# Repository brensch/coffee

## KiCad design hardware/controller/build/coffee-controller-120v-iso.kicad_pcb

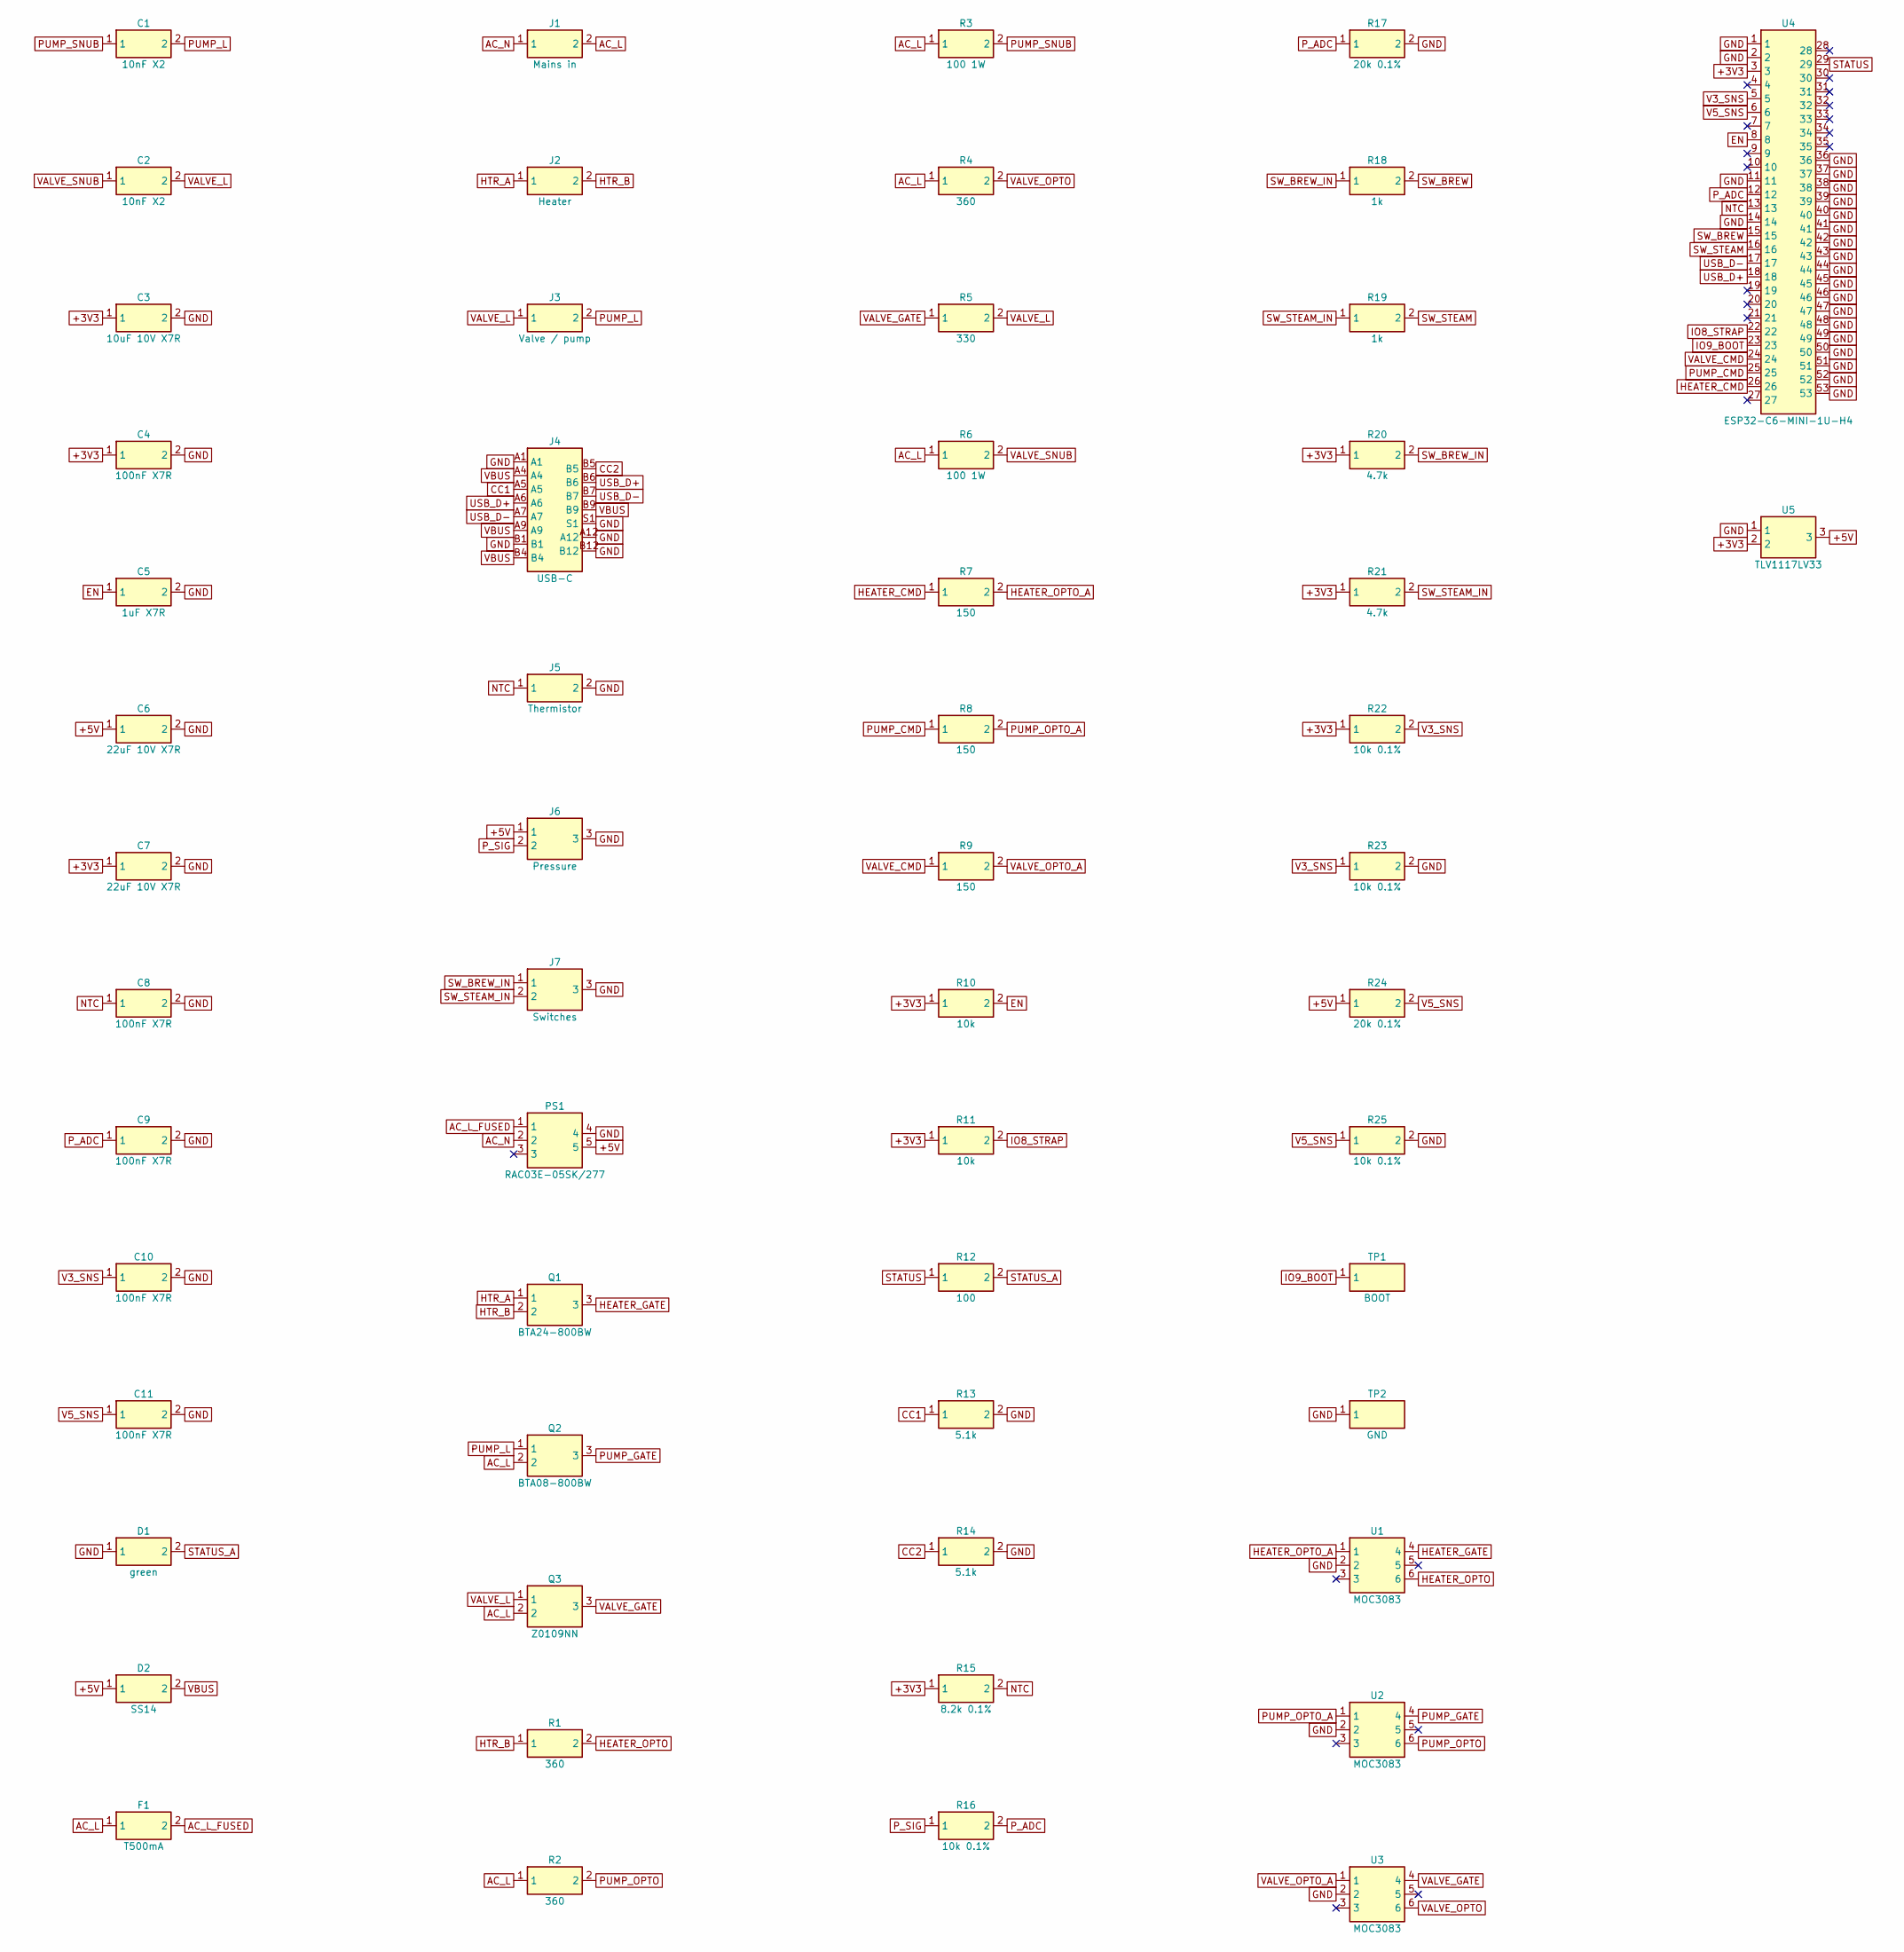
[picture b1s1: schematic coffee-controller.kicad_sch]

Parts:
C1, C2: 10nF X2; C_2220_Murata_GA355; MPN Murata GA355QR7GB103KW01L (10 nF X2 250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
C3: 10uF 10V X7R; C_0805_2012Metric
C4, C8, C9, C10, C11: 100nF X7R; C_0603_1608Metric
C5: 1uF X7R; C_0603_1608Metric
C6, C7: 22uF 10V X7R; C_0805_2012Metric; MPN Murata GRM21BZ71A226ME15L
D1: green; LED_0603_1608Metric
D2: SS14; D_SMA; MPN SS14
F1: T500mA; Fuse_Littelfuse_372_D8.50mm; MPN Littelfuse 37205000411 (TR5, 500 mA slo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
J1: Mains in; TerminalBlock_Phoenix_MKDS-1,5-2-5.08_1x02_P5.08mm_Horizont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; MPN Phoenix Contact MKDS 1,5/2-5.08 (171572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
J2: Heater; TerminalBlock_Phoenix_MKDS-3-2-5.08_1x02_P5.08mm_Horizontal; MPN Phoenix Contact MKDS 3/2-5.08 (1711725)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
J3: Valve / pump; TerminalBlock_Phoenix_MKDS-1,5-2-5.08_1x02_P5.08mm_Horizont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; MPN Phoenix Contact MKDS 1,5/2-5.08 (171572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
J4: USB-C; USB_C_Receptacle_GCT_USB4105-xx-A_16P_TopMnt_Horizontal; MPN GCT USB4105-GF-A
J5: Thermistor; JST_PH_B2B-PH-K_1x02_P2.00mm_Vertical
J6: Pressure; JST_PH_B3B-PH-K_1x03_P2.00mm_Vertical
J7: Switches; JST_PH_B3B-PH-K_1x03_P2.00mm_Vertical
PS1: RAC03E-05SK/277; RAC03E-K_277; MPN RECOM RAC03E-05SK/277
Q1: BTA24-800BW; TO-220-3_Vertical_Drill1.2; MPN ST BTA24-800BWRG (25 A, 800 V, insulate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
Q2: BTA08-800BW; TO-220-3_Vertical_Drill1.2; MPN ST BTA08-800BWRG (8 A, 800 V, insulated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
Q3: Z0109NN; SOT-223-3_TabPin2; MPN ST Z0109NN5AA4 (1 A, 800 V, IGT 10 mA)
R1, R2, R4: 360; R_1206_3216Metric
R3, R6: 100 1W; R_2512_6332Metric
R5: 330; R_1206_3216Metric
R7, R8, R9: 150; R_0603_1608Metric
R10, R11: 10k; R_0603_1608Metric
R12: 100; R_0603_1608Metric
R13, R14: 5.1k; R_0603_1608Metric
R15: 8.2k 0.1%; R_0603_1608Metric
R16, R22, R23, R25: 10k 0.1%; R_0603_1608Metric
R17, R24: 20k 0.1%; R_0603_1608Metric
R18, R19: 1k; R_0603_1608Metric
R20, R21: 4.7k; R_0603_1608Metric
TP1: BOOT; TestPoint_Pad_D1.5mm
TP2: GND; TestPoint_Pad_D1.5mm
U1, U2, U3: MOC3083; DIP-6_W10.16mm; MPN onsemi MOC3083TVM (0.4" leads)
U4: ESP32-C6-MINI-1U-H4; ESP32-C6-MINI-1U; MPN ESP32-C6-MINI-1U-H4
U5: TLV1117LV33; SOT-223-3_TabPin2; MPN TI TLV1117LV33DCYR

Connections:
+3V3: C3.1, C4.1, C7.1, R10.1, R11.1, R15.1, R20.1, R21.1, R22.1, U4.3, U5.2
+5V: C6.1, D2.1, J6.1, PS1.5, R24.1, U5.3
AC_L: F1.1, J1.2, Q2.2, Q3.2, R2.1, R3.1, R4.1, R6.1
AC_L_FUSED: F1.2, PS1.1
AC_N: J1.1, PS1.2
CC1: J4.A5, R13.1
CC2: J4.B5, R14.1
EN: C5.1, R10.2, U4.8
GND: C3.2, C4.2, C5.2, C6.2, C7.2, C8.2, C9.2, C10.2, C11.2, D1.1, J4.A1, J4.A12, J4.B1, J4.B12, J4.S1, J5.2, J6.3, J7.3, PS1.4, R13.2, R14.2, R17.2, R23.2, R25.2, TP2.1, U1.2, U2.2, U3.2, U4.1, U4.2, U4.11, U4.14, U4.36, U4.37, U4.38, U4.39, U4.40, U4.41, U4.42, U4.43, U4.44, U4.45, U4.46, U4.47, U4.48, U4.49, U4.50, U4.51, U4.52, U4.53, U5.1
HEATER_CMD: R7.1, U4.26
HEATER_GATE: Q1.3, U1.4
HEATER_OPTO: R1.2, U1.6
HEATER_OPTO_A: R7.2, U1.1
HTR_A: J2.1, Q1.1
HTR_B: J2.2, Q1.2, R1.1
IO8_STRAP: R11.2, U4.22
IO9_BOOT: TP1.1, U4.23
NTC: C8.1, J5.1, R15.2, U4.13
PUMP_CMD: R8.1, U4.25
PUMP_GATE: Q2.3, U2.4
PUMP_L: C1.2, J3.2, Q2.1
PUMP_OPTO: R2.2, U2.6
PUMP_OPTO_A: R8.2, U2.1
PUMP_SNUB: C1.1, R3.2
P_ADC: C9.1, R16.2, R17.1, U4.12
P_SIG: J6.2, R16.1
STATUS: R12.1, U4.29
STATUS_A: D1.2, R12.2
SW_BREW: R18.2, U4.15
SW_BREW_IN: J7.1, R18.1, R20.2
SW_STEAM: R19.2, U4.16
SW_STEAM_IN: J7.2, R19.1, R21.2
USB_D+: J4.A6, J4.B6, U4.18
USB_D-: J4.A7, J4.B7, U4.17
V3_SNS: C10.1, R22.2, R23.1, U4.5
V5_SNS: C11.1, R24.2, R25.1, U4.6
VALVE_CMD: R9.1, U4.24
VALVE_GATE: Q3.3, R5.1, U3.4
VALVE_L: C2.2, J3.1, Q3.1, R5.2
VALVE_OPTO: R4.2, U3.6
VALVE_OPTO_A: R9.2, U3.1
VALVE_SNUB: C2.1, R6.2
VBUS: D2.2, J4.A4, J4.A9, J4.B4, J4.B9

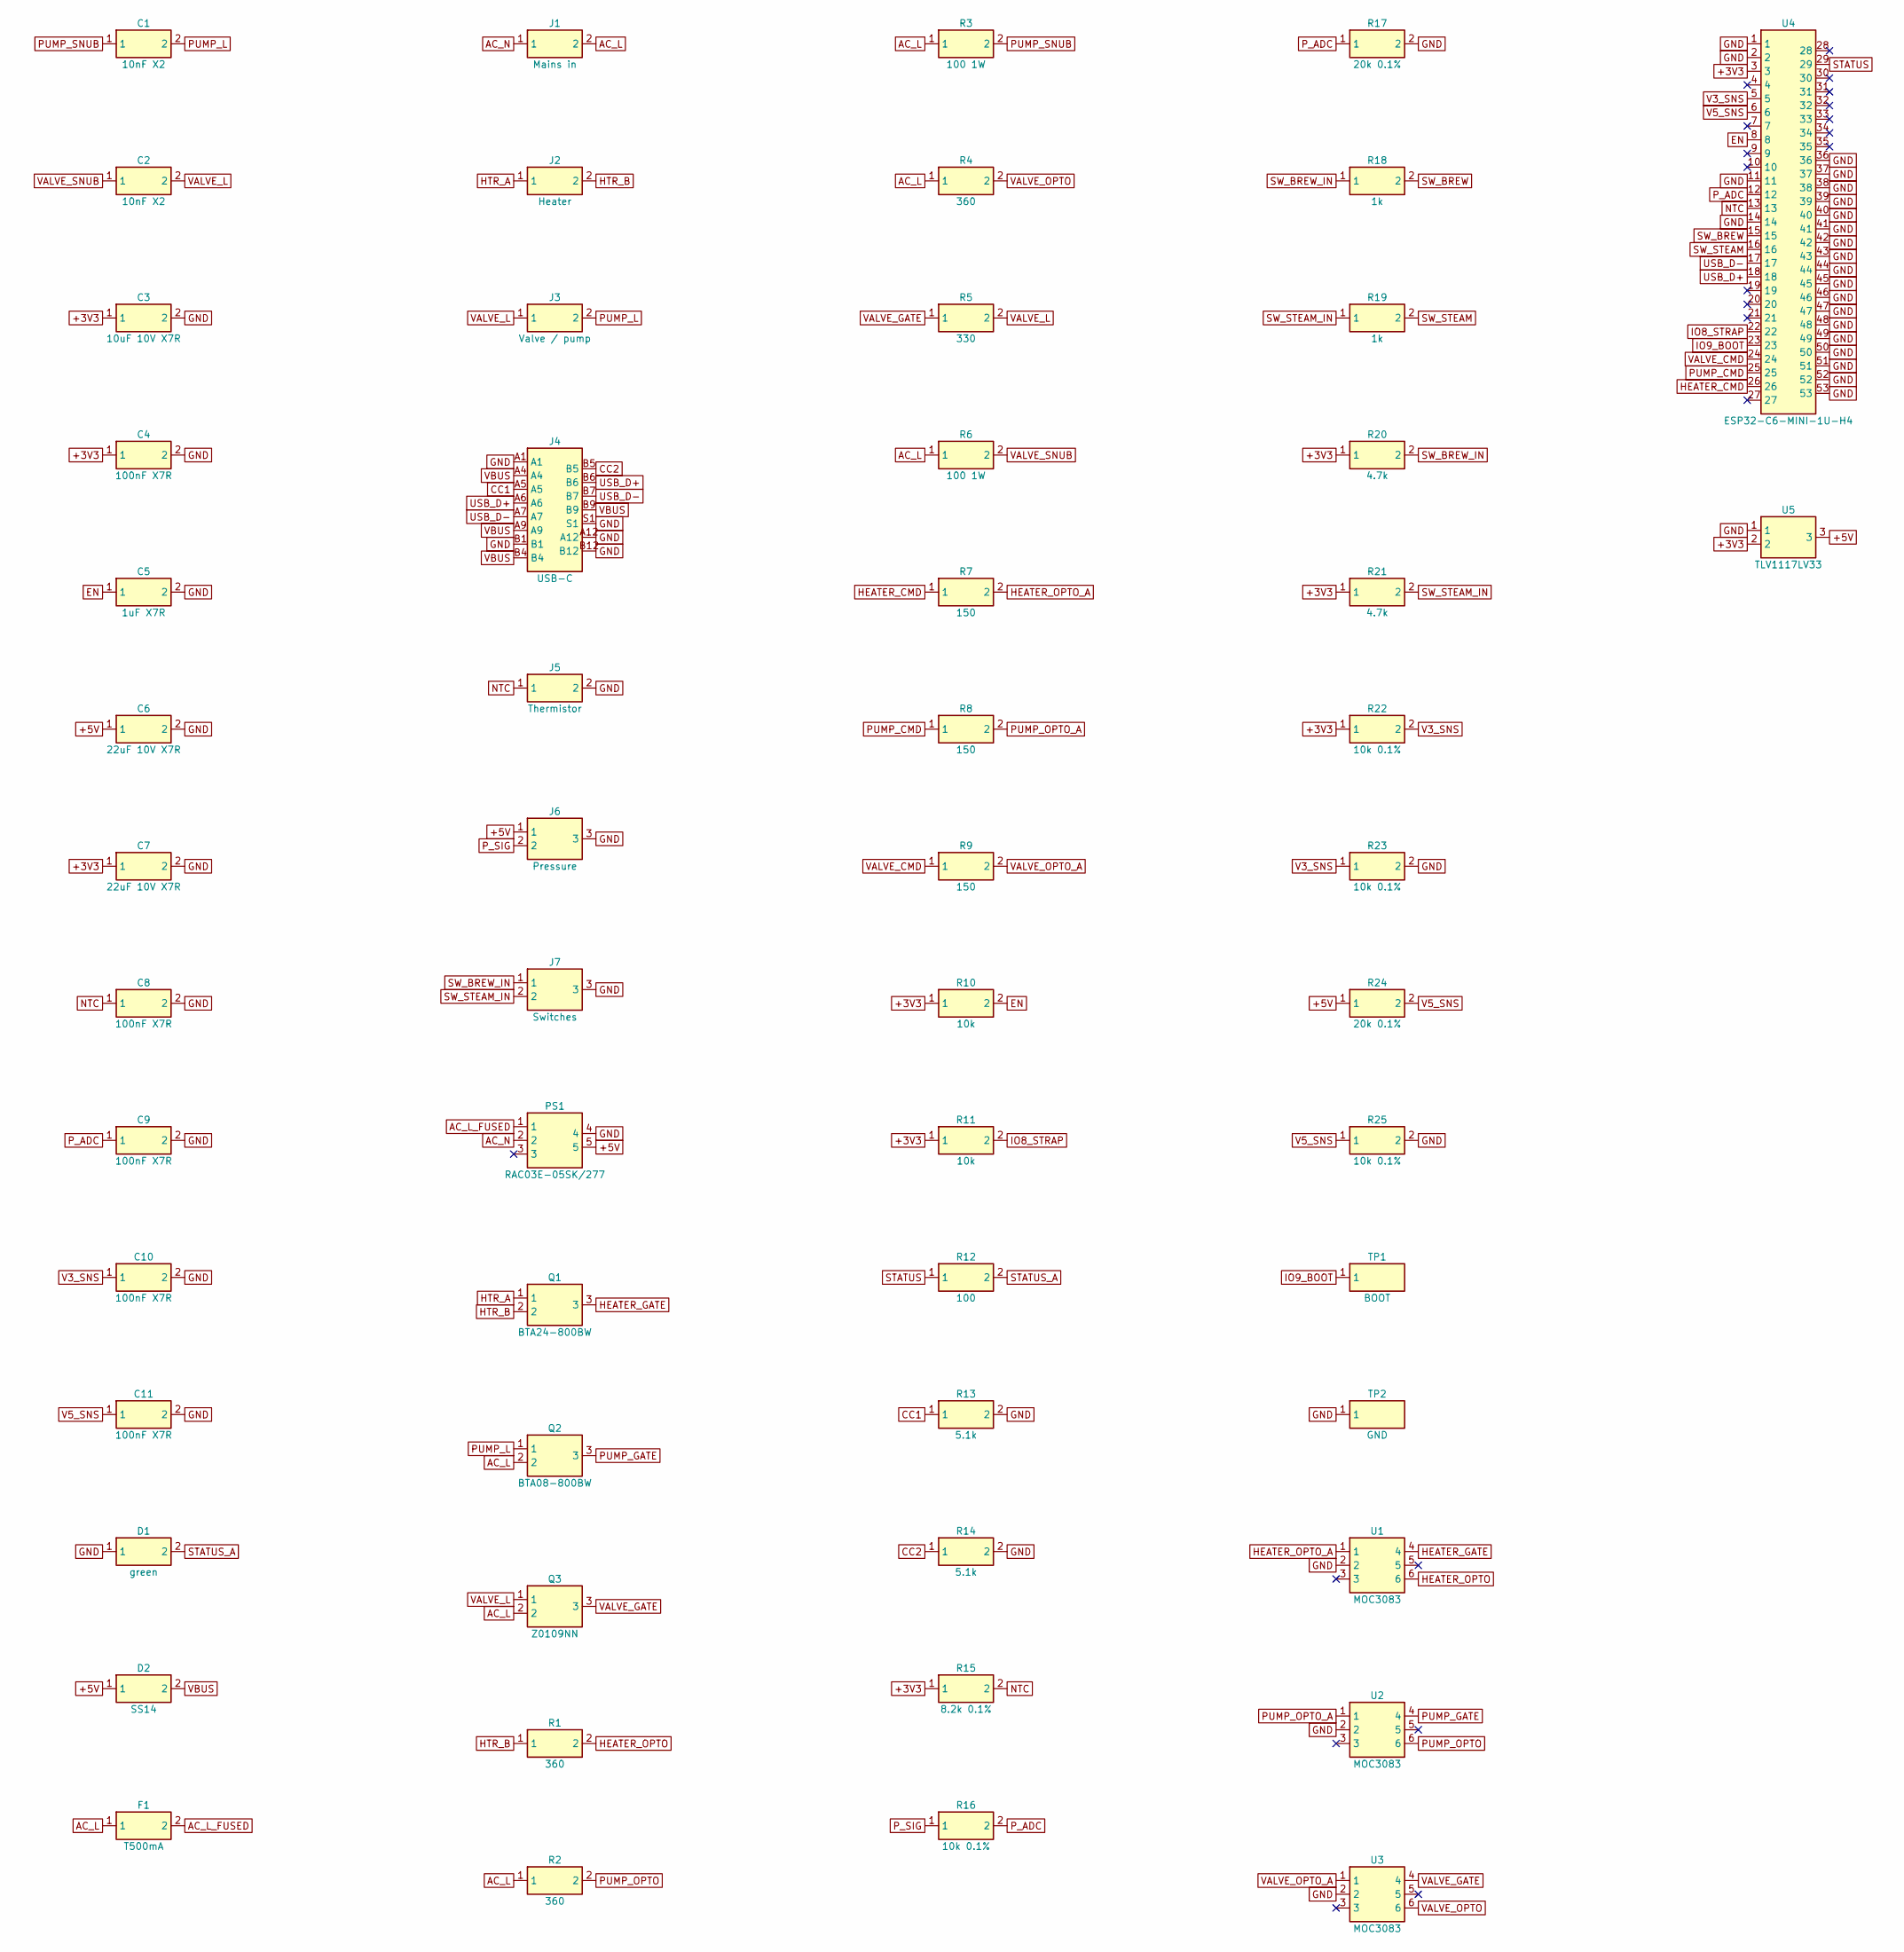
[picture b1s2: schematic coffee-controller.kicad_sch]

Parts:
C1, C2: 10nF X2; C_2220_Murata_GA355; MPN Murata GA355QR7GB103KW01L (10 nF X2 250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
C3: 10uF 10V X7R; C_0805_2012Metric
C4, C8, C9, C10, C11: 100nF X7R; C_0603_1608Metric
C5: 1uF X7R; C_0603_1608Metric
C6, C7: 22uF 10V X7R; C_0805_2012Metric; MPN Murata GRM21BZ71A226ME15L
D1: green; LED_0603_1608Metric
D2: SS14; D_SMA; MPN SS14
F1: T500mA; Fuse_Littelfuse_372_D8.50mm; MPN Littelfuse 37205000411 (TR5, 500 mA slo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
J1: Mains in; TerminalBlock_Phoenix_MKDS-1,5-2-5.08_1x02_P5.08mm_Horizont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; MPN Phoenix Contact MKDS 1,5/2-5.08 (171572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
J2: Heater; TerminalBlock_Phoenix_MKDS-3-2-5.08_1x02_P5.08mm_Horizontal; MPN Phoenix Contact MKDS 3/2-5.08 (1711725)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
J3: Valve / pump; TerminalBlock_Phoenix_MKDS-1,5-2-5.08_1x02_P5.08mm_Horizont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; MPN Phoenix Contact MKDS 1,5/2-5.08 (171572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
J4: USB-C; USB_C_Receptacle_GCT_USB4105-xx-A_16P_TopMnt_Horizontal; MPN GCT USB4105-GF-A
J5: Thermistor; JST_PH_B2B-PH-K_1x02_P2.00mm_Vertical
J6: Pressure; JST_PH_B3B-PH-K_1x03_P2.00mm_Vertical
J7: Switches; JST_PH_B3B-PH-K_1x03_P2.00mm_Vertical
PS1: RAC03E-05SK/277; RAC03E-K_277; MPN RECOM RAC03E-05SK/277
Q1: BTA24-800BW; TO-220-3_Vertical_Drill1.2; MPN ST BTA24-800BWRG (25 A, 800 V, insulate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
Q2: BTA08-800BW; TO-220-3_Vertical_Drill1.2; MPN ST BTA08-800BWRG (8 A, 800 V, insulated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
Q3: Z0109NN; SOT-223-3_TabPin2; MPN ST Z0109NN5AA4 (1 A, 800 V, IGT 10 mA)
R1, R2, R4: 360; R_1206_3216Metric
R3, R6: 100 1W; R_2512_6332Metric
R5: 330; R_1206_3216Metric
R7, R8, R9: 150; R_0603_1608Metric
R10, R11: 10k; R_0603_1608Metric
R12: 100; R_0603_1608Metric
R13, R14: 5.1k; R_0603_1608Metric
R15: 8.2k 0.1%; R_0603_1608Metric
R16, R22, R23, R25: 10k 0.1%; R_0603_1608Metric
R17, R24: 20k 0.1%; R_0603_1608Metric
R18, R19: 1k; R_0603_1608Metric
R20, R21: 4.7k; R_0603_1608Metric
TP1: BOOT; TestPoint_Pad_D1.5mm
TP2: GND; TestPoint_Pad_D1.5mm
U1, U2, U3: MOC3083; DIP-6_W10.16mm; MPN onsemi MOC3083TVM (0.4" leads)
U4: ESP32-C6-MINI-1U-H4; ESP32-C6-MINI-1U; MPN ESP32-C6-MINI-1U-H4
U5: TLV1117LV33; SOT-223-3_TabPin2; MPN TI TLV1117LV33DCYR

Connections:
+3V3: C3.1, C4.1, C7.1, R10.1, R11.1, R15.1, R20.1, R21.1, R22.1, U4.3, U5.2
+5V: C6.1, D2.1, J6.1, PS1.5, R24.1, U5.3
AC_L: F1.1, J1.2, Q2.2, Q3.2, R2.1, R3.1, R4.1, R6.1
AC_L_FUSED: F1.2, PS1.1
AC_N: J1.1, PS1.2
CC1: J4.A5, R13.1
CC2: J4.B5, R14.1
EN: C5.1, R10.2, U4.8
GND: C3.2, C4.2, C5.2, C6.2, C7.2, C8.2, C9.2, C10.2, C11.2, D1.1, J4.A1, J4.A12, J4.B1, J4.B12, J4.S1, J5.2, J6.3, J7.3, PS1.4, R13.2, R14.2, R17.2, R23.2, R25.2, TP2.1, U1.2, U2.2, U3.2, U4.1, U4.2, U4.11, U4.14, U4.36, U4.37, U4.38, U4.39, U4.40, U4.41, U4.42, U4.43, U4.44, U4.45, U4.46, U4.47, U4.48, U4.49, U4.50, U4.51, U4.52, U4.53, U5.1
HEATER_CMD: R7.1, U4.26
HEATER_GATE: Q1.3, U1.4
HEATER_OPTO: R1.2, U1.6
HEATER_OPTO_A: R7.2, U1.1
HTR_A: J2.1, Q1.1
HTR_B: J2.2, Q1.2, R1.1
IO8_STRAP: R11.2, U4.22
IO9_BOOT: TP1.1, U4.23
NTC: C8.1, J5.1, R15.2, U4.13
PUMP_CMD: R8.1, U4.25
PUMP_GATE: Q2.3, U2.4
PUMP_L: C1.2, J3.2, Q2.1
PUMP_OPTO: R2.2, U2.6
PUMP_OPTO_A: R8.2, U2.1
PUMP_SNUB: C1.1, R3.2
P_ADC: C9.1, R16.2, R17.1, U4.12
P_SIG: J6.2, R16.1
STATUS: R12.1, U4.29
STATUS_A: D1.2, R12.2
SW_BREW: R18.2, U4.15
SW_BREW_IN: J7.1, R18.1, R20.2
SW_STEAM: R19.2, U4.16
SW_STEAM_IN: J7.2, R19.1, R21.2
USB_D+: J4.A6, J4.B6, U4.18
USB_D-: J4.A7, J4.B7, U4.17
V3_SNS: C10.1, R22.2, R23.1, U4.5
V5_SNS: C11.1, R24.2, R25.1, U4.6
VALVE_CMD: R9.1, U4.24
VALVE_GATE: Q3.3, R5.1, U3.4
VALVE_L: C2.2, J3.1, Q3.1, R5.2
VALVE_OPTO: R4.2, U3.6
VALVE_OPTO_A: R9.2, U3.1
VALVE_SNUB: C2.1, R6.2
VBUS: D2.2, J4.A4, J4.A9, J4.B4, J4.B9

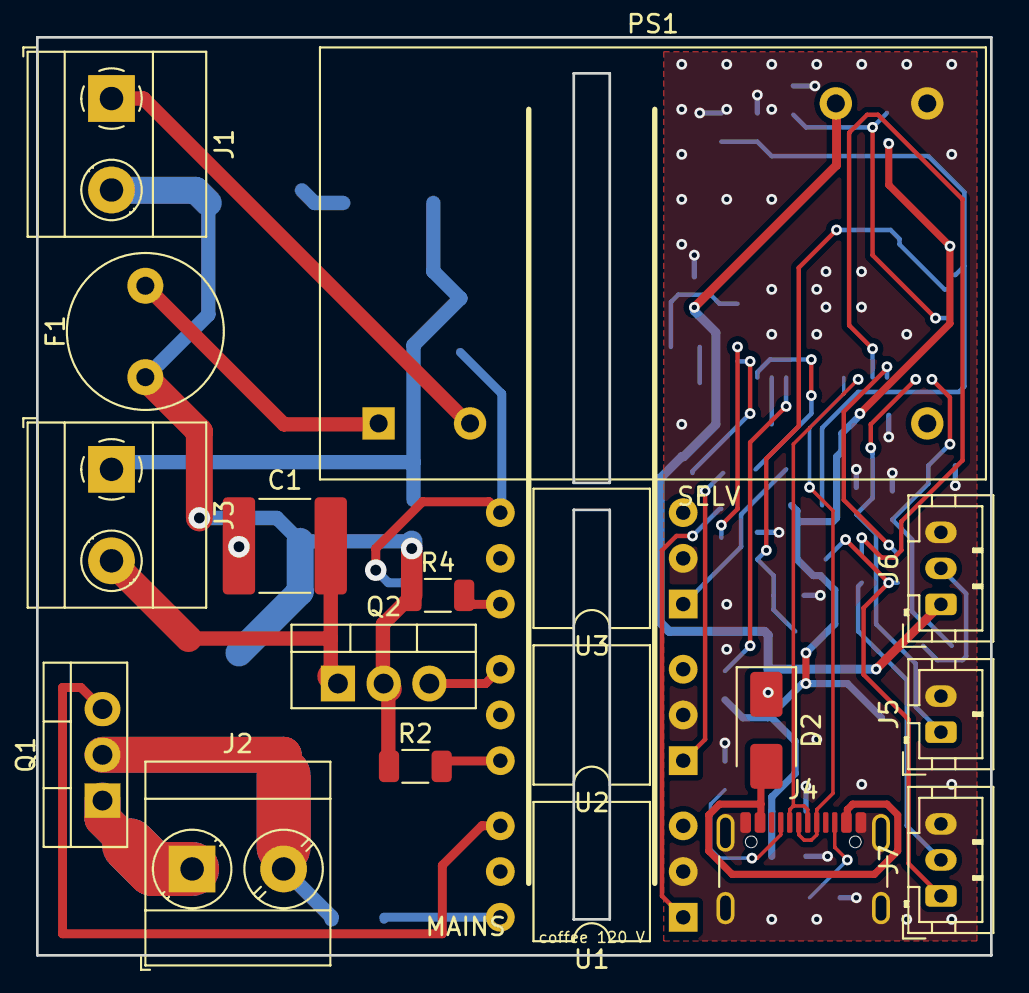
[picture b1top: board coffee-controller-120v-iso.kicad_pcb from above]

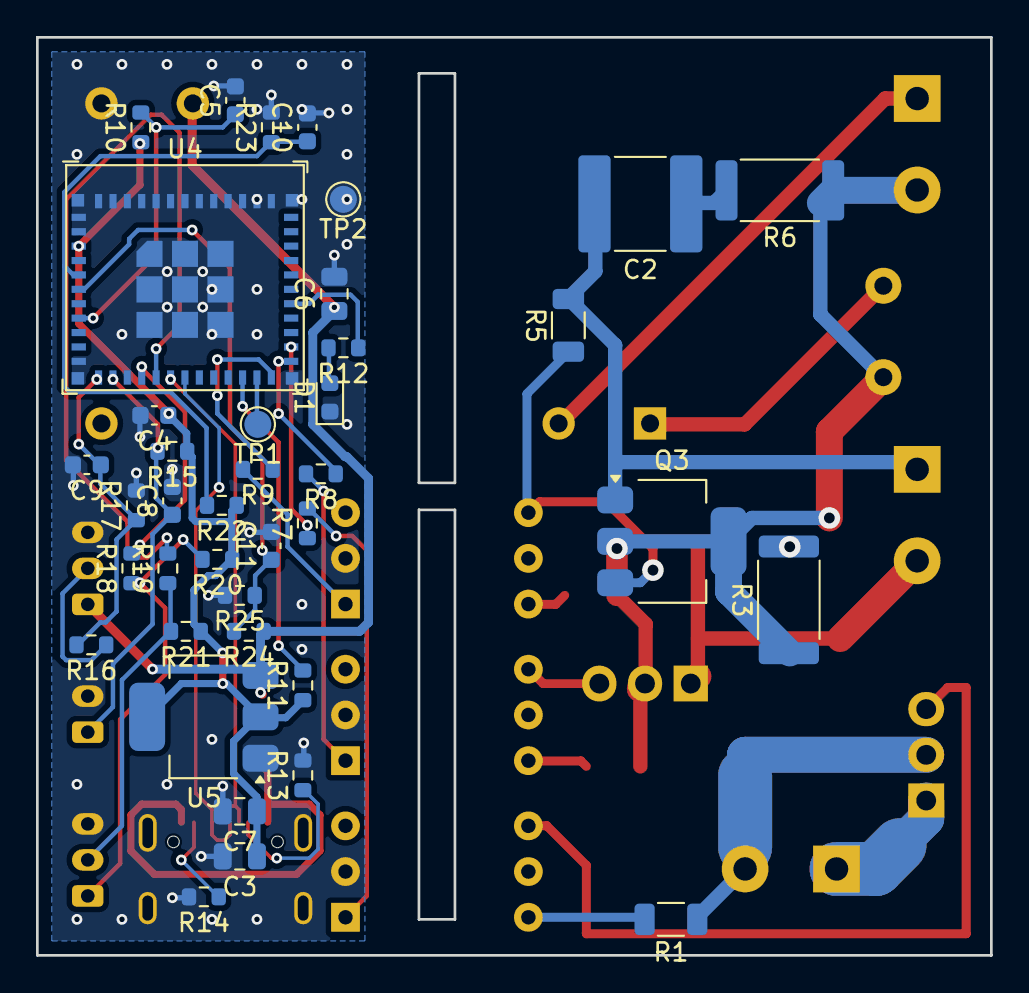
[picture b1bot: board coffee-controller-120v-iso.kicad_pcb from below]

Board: 2 copper layers, 53.0 x 51.0 mm, 57 parts (39 on the bottom side), 43 nets.

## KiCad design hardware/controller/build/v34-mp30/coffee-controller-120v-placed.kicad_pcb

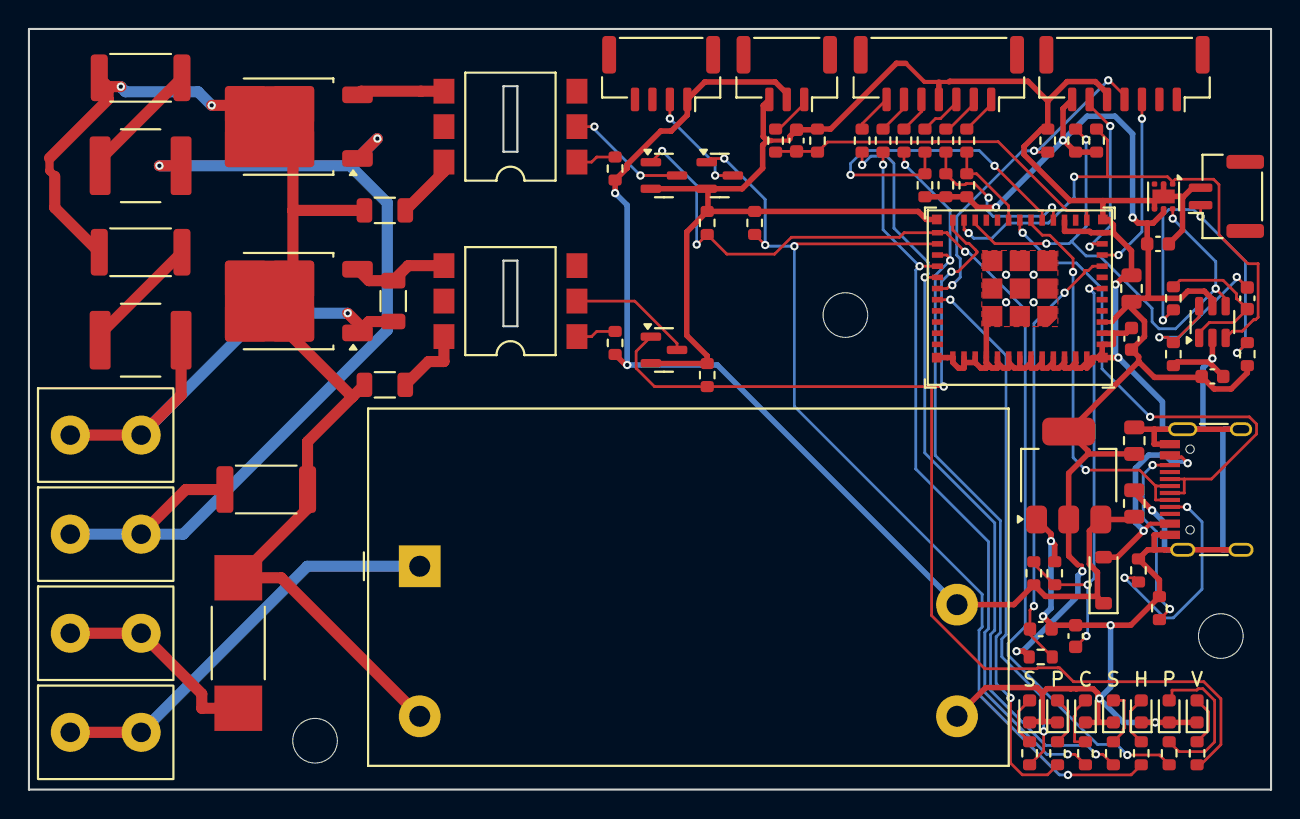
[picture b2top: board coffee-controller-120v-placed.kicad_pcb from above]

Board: 2 copper layers, 89.0 x 54.5 mm, 87 parts (1 on the bottom side), 59 nets.

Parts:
C3: 10uF 25V X5R; C_0805_2012Metric
C4, C11, C13, C14: 100nF X7R; C_0603_1608Metric
C5, C12: 1uF X5R; C_0603_1608Metric
C6, C7: 22uF 25V X5R; C_0805_2012Metric
C9: 22nF X7R; C_0603_1608Metric
C15, C16: 22nF X2; C_2220_Murata_GA355
D1, D3, D4, D5, D6, D7, D8: red; LED_0603_1608Metric
D2: B5819W; D_SOD-123
F1: 2A T; Fuse_Littelfuse_Nano2_443
H1, H2, H3: M3; MountingHole_3.2mm_M3
J2: Heater SSR; JST_GH_SM04B-GHS-TB_1x04-1MP_P1.25mm_Horizontal
J4: USB-C; USB_C_Receptacle_HRO_TYPE-C-31-M-12
J5: Thermocouple; JST_GH_SM02B-GHS-TB_1x02-1MP_P1.25mm_Horizontal
J6: Pressure; JST_GH_SM03B-GHS-TB_1x03-1MP_P1.25mm_Horizontal
J7: Front panel; JST_GH_SM07B-GHS-TB_1x07-1MP_P1.25mm_Horizontal
J10: Scale; JST_GH_SM07B-GHS-TB_1x07-1MP_P1.25mm_Horizontal
J12: N; FASTON_TE_63824-1
J13: L; FASTON_TE_63824-1
J14: P; FASTON_TE_63824-1
J15: 3; FASTON_TE_63824-1
PS1: IRM-10-5; Converter_ACDC_MeanWell_IRM-10-xx_THT
Q1, Q2, Q3: AO3400A; SOT-23
Q5: T435-600B; TO-252-2
Q6: T410-600B; TO-252-2
R4, R5, R6: 3.3k; R_0603_1608Metric
R10, R20, R21, R25, R28, R36: 10k; R_0603_1608Metric
R11, R46: 4.7k; R_0603_1608Metric
R12, R18, R19, R29, R37, R38, R39, R40, R41, R42, R43, R44: 1k; R_0603_1608Metric
R13, R14: 5.1k; R_0603_1608Metric
R16: 47k; R_0603_1608Metric
R17: 100k; R_0603_1608Metric
R24: 20k; R_0603_1608Metric
R30, R31, R32, R47, R48: 330; R_0603_1608Metric
R45: 10M; R_0603_1608Metric
R49, R50: 330; R_1206_3216Metric
R51, R52: 100 1W; R_2512_6332Metric
R53: 1k; R_1206_3216Metric
R54: 51k 500V; R_2512_6332Metric
TP1: BOOT; TestPoint_Pad_D1.0mm
U4: ESP32-C6-MINI-1U-H4; ESP32-C6-MINI-1U
U5: TLV1117LV33DCYR; SOT-223-3_TabPin2
U6: MCP3421A0T-E/CH; SOT-23-6
U7: TMP117AIDRVR; WSON-6-1EP_2x2mm_P0.65mm_EP1x1.6mm
U8, U9: MOC3083SR2M; SMDIP-6_W9.53mm_Clearance8mm

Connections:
+3V3: C3.1, C4.1, C7.1, C13.1, C14.1, J10.7, R10.1, R11.1, R20.1, R21.1, R28.1, R45.1, R46.1, U4.3, U5.2, U6.5, U7.5
+5V: C6.1, D2.1, J2.1, J6.2, PS1.4, R24.1, R47.1, R48.1, U5.3
AC_L: F1.1, J13.1
AC_L_F: F1.2, PS1.2, Q5.2, Q6.2, R49.1, R50.1, R51.1, R52.1, R54.1
AC_N: J12.1, PS1.1
CC1: J4.A5, R13.1
CC2: J4.B5, R14.1
EN: C5.1, R10.2, U4.8
GND: C3.2, C4.2, C5.2, C6.2, C7.2, C9.2, C11.2, C13.2, C14.2, D1.1, D3.1, D4.1, D5.1, D6.1, D7.1, D8.1, J4.A1, J4.A12, J4.B1, J4.B12, J4.S1, J5.2, J6.3, J7.4, J10.5, PS1.3, Q1.2, Q2.2, Q3.2, R4.2, R5.2, R6.2, R13.2, R14.2, R17.2, R25.2, R36.2, R44.1, U4.1, U4.2, U4.11, U4.14, U4.36, U4.37, U4.38, U4.39, U4.40, U4.41, U4.42, U4.43, U4.44, U4.45, U4.46, U4.47, U4.48, U4.49, U4.50, U4.51, U4.52, U4.53, U5.1, U6.2, U7.2, U7.4, U7.7
HEATER_CMD: Q1.1, R4.1, R40.1, U4.26
HEATER_CMD_IND: D6.2, R40.2
HEATER_OUT: J2.2, Q1.3
I2C_SCL: R46.2, TP1.1, U4.23, U6.3, U7.1
I2C_SDA: R11.2, U4.22, U6.4, U7.6
LED_COFFEE: J7.6, R31.2
LED_COFFEE_IO: R31.1, R38.1, U4.28
LED_COFFEE_IO_IND: D4.2, R38.2
LED_PWR: J7.5, R30.2
LED_PWR_IO: R30.1, R37.1, U4.27
LED_PWR_IO_IND: D3.2, R37.2
LED_STEAM: J7.7, R32.2
LED_STEAM_IO: R32.1, R39.1, U4.29
LED_STEAM_IO_IND: D5.2, R39.2
PUMP_CMD: Q2.1, R5.1, R41.1, U4.25
PUMP_CMD_IND: D7.2, R41.2
PUMP_G: Q5.3, U8.4
PUMP_LED_A: R47.2, U8.1
PUMP_O6: R49.2, U8.6
PUMP_OUT: Q2.3, U8.2
PUMP_SNUB: C15.1, R51.2
PUMP_SW: C15.2, J14.1, Q5.1, R54.2
P_ADC: C9.1, R16.2, R17.1, U4.12
P_SIG: J6.1, R16.1
SCALE_DOUT1: J10.3, U4.9
SCALE_DOUT2: J10.6, U4.10
SCALE_SCK: J10.4, R36.1, U4.30
STATUS: R12.1, U4.31
STATUS_A: D1.2, R12.2
SW_BREW: R18.2, R20.2, U4.15
SW_BREW_IN: J7.2, R18.1
SW_POWER: R28.2, R29.2, U4.19
SW_POWER_IN: J7.1, R29.1
SW_STEAM: R19.2, R21.2, U4.16
SW_STEAM_IN: J7.3, R19.1
TC_INN: C12.2, R44.2, U6.6
TC_INP: C12.1, R43.2, U6.1
TC_P: J5.1, R43.1, R45.2
USB_D+: J4.A6, J4.B6, U4.18
USB_D-: J4.A7, J4.B7, U4.17
V5_SNS: C11.1, R24.2, R25.1, U4.6
VALVE_CMD: Q3.1, R6.1, R42.1, U4.24
VALVE_CMD_IND: D8.2, R42.2
VALVE_G: Q6.3, R53.1, U9.4
VALVE_LED_A: R48.2, U9.1
VALVE_O6: R50.2, U9.6
VALVE_OUT: Q3.3, U9.2
VALVE_SNUB: C16.1, R52.2
VALVE_SW: C16.2, J15.1, Q6.1, R53.2
VBUS: D2.2, J4.A4, J4.A9, J4.B4, J4.B9
